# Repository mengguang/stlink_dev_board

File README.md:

# stlink_dev_board
I know nothing about this project.

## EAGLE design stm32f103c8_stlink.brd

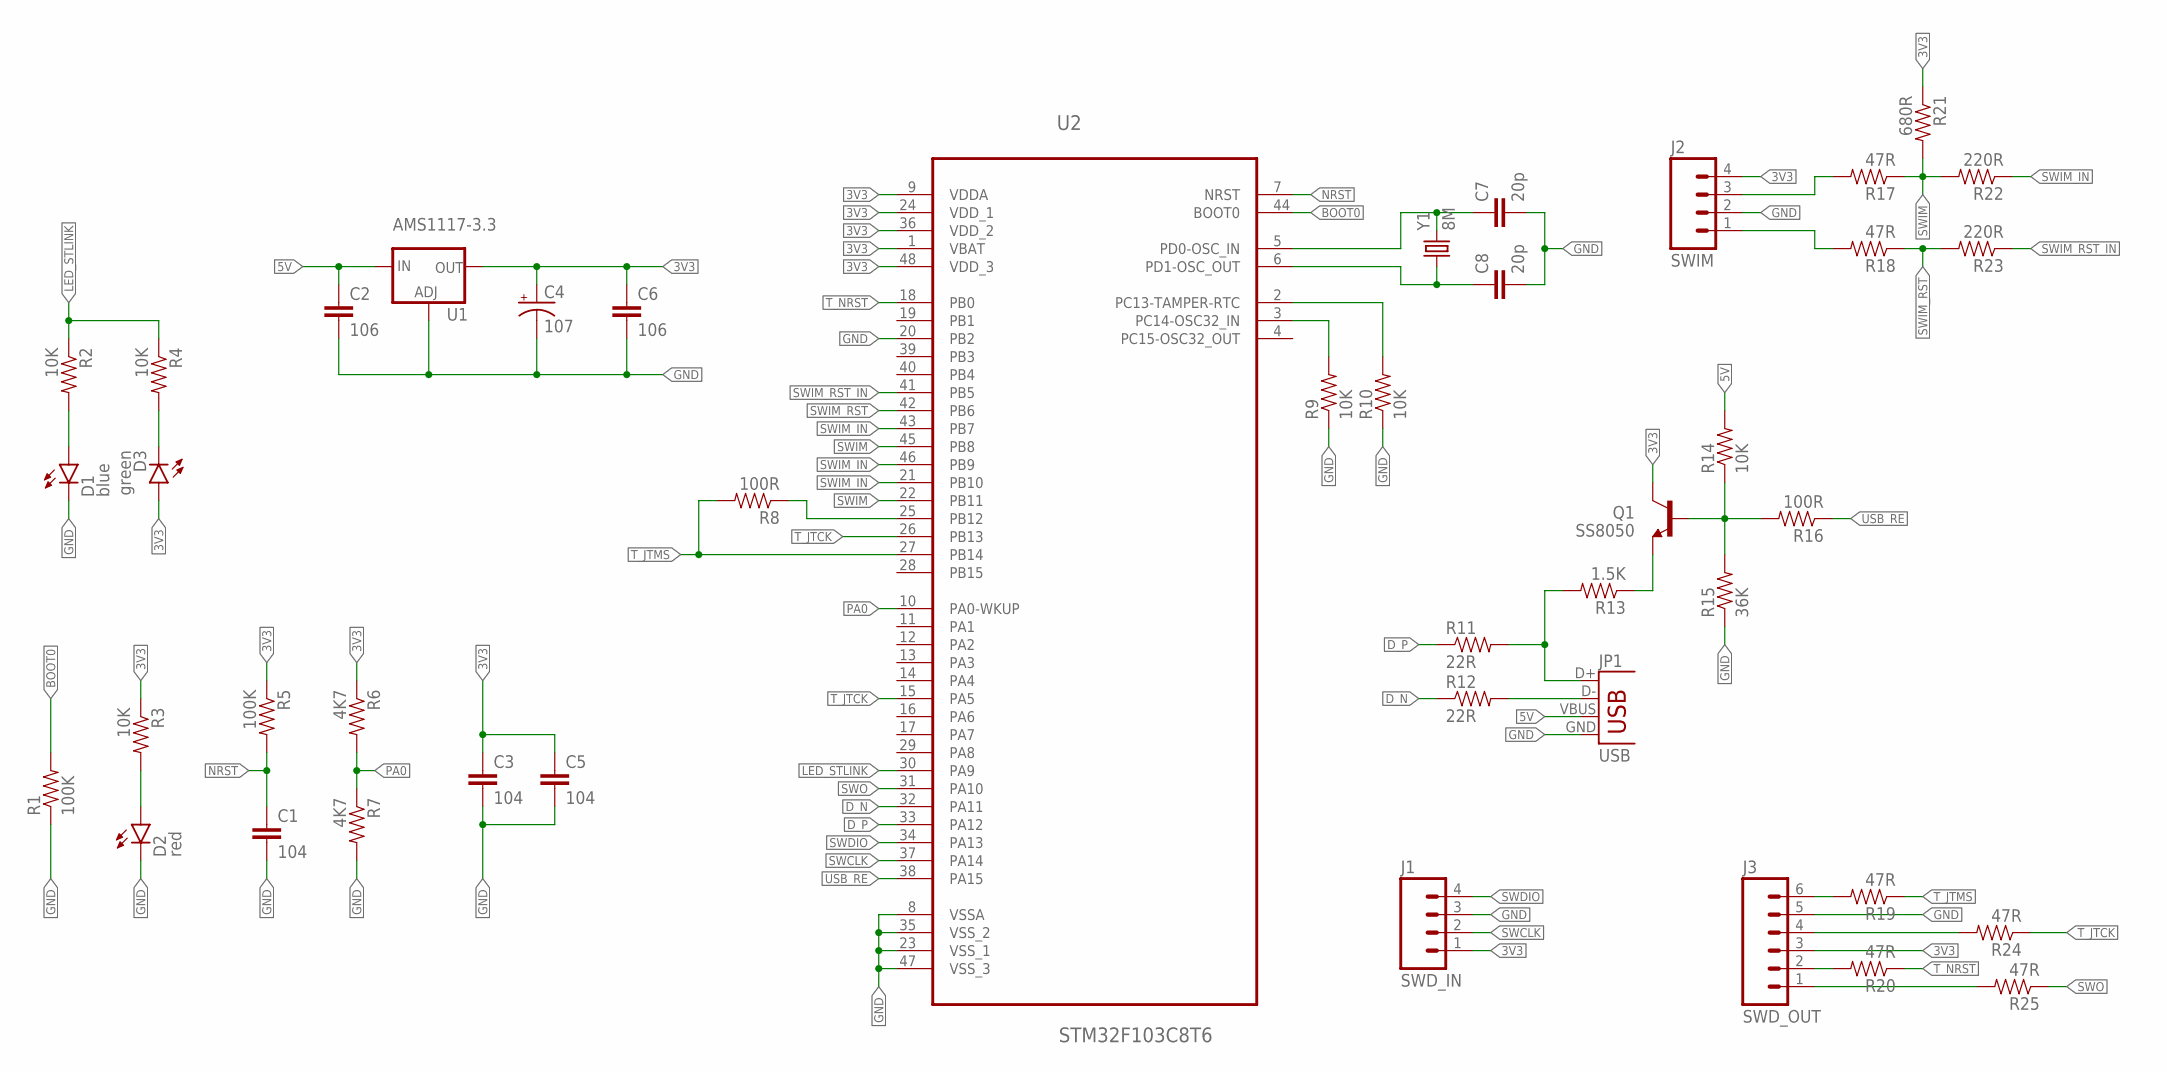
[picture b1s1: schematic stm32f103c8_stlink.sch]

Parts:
C1, C3, C5: 104; 0603-CAP
C2, C6: 106; 0603-CAP
C4: 107; EIA3528
C7, C8: 20p; 0603-CAP
D1: blue; LED-0603-SEEED
D2: red; LED-0603-SEEED
D3: green; LED-0603-SEEED
J1: SWD_IN; 1X04_NO_SILK
J2: SWIM; 1X04_NO_SILK
J3: SWD_OUT; 1X06_NO_SILK
JP1: USB; MICROUSB-U-F-M5DD-Y-1
Q1: SS8050; SOT23-3
R1, R5: 100K; 0603-RES
R2, R3, R4, R9, R10, R14: 10K; 0603-RES
R6, R7: 4K7; 0603-RES
R8, R16: 100R; 0603-RES
R11, R12: 22R; 0603-RES
R13: 1.5K; 0603-RES
R15: 36K; 0603-RES
R17, R18, R19, R20, R24, R25: 47R; 0603-RES
R21: 680R; 0603-RES
R22, R23: 220R; 0603-RES
U1: AMS1117-3.3; SOT223
U2: STM32F103C8T6; LQFP-48
Y1: 8M; HC49US

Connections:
3V3: C3.1, C4.A (+), C5.1, C6.1, D3.+ (A), J1.1, J2.4, J3.3, Q1.3 (C), R3.1, R5.1, R6.1, R21.1, U1.2 (OUT), U1.4 (OUT), U2.1 (VBAT), U2.9 (VDDA), U2.24 (VDD_1), U2.36 (VDD_2), U2.48 (VDD_3)
5V: C2.1, JP1.VBUS, R14.2, U1.3 (IN)
BOOT0: R1.2, U2.44 (BOOT0)
D_N: R12.1, U2.32 (PA11)
D_P: R11.1, U2.33 (PA12)
GND: C1.2, C2.2, C3.2, C4.C (-), C5.2, C6.2, C7.2, C8.2, D1.- (C), D2.- (C), J1.3, J2.2, J3.5, JP1.GND, R1.1, R7.2, R9.1, R10.1, R15.1, U1.1 (ADJ), U2.8 (VSSA), U2.20 (PB2), U2.23 (VSS_1), U2.35 (VSS_2), U2.47 (VSS_3)
LED_STLINK: R2.1, R4.1, U2.30 (PA9)
unnamed: J3.6, R19.2
unnamed: J2.3, R17.2
unnamed: C7.1, U2.5 (PD0-OSC_IN), Y1.2
unnamed: C8.1, U2.6 (PD1-OSC_OUT), Y1.1
unnamed: D2.+ (A), R3.2
unnamed: Q1.2 (E), R13.1
unnamed: D1.+ (A), R2.2
unnamed: R10.2, U2.2 (PC13-TAMPER-RTC)
unnamed: R9.2, U2.3 (PC14-OSC32_IN)
unnamed: D3.- (C), R4.2
unnamed: Q1.1 (B), R14.1, R15.2, R16.2
unnamed: R8.1, U2.25 (PB12)
unnamed: J2.1, R18.2
unnamed: J3.4, R24.2
unnamed: J3.2, R20.2
unnamed: J3.1, R25.2
NRST: C1.1, R5.2, U2.7 (NRST)
PA0: R6.2, R7.1, U2.10 (PA0-WKUP)
SWCLK: J1.2, U2.37 (PA14)
SWDIO: J1.4, U2.34 (PA13)
SWIM: R17.1, R21.2, R22.2, U2.22 (PB11), U2.45 (PB8)
SWIM_IN: R22.1, U2.21 (PB10), U2.43 (PB7), U2.46 (PB9)
SWIM_RST: R18.1, R23.2, U2.42 (PB6)
SWIM_RST_IN: R23.1, U2.41 (PB5)
SWO: R25.1, U2.31 (PA10)
T_JTCK: R24.1, U2.15 (PA5), U2.26 (PB13)
T_JTMS: R8.2, R19.1, U2.27 (PB14)
T_NRST: R20.1, U2.18 (PB0)
USB_N: JP1.D-, R12.2
USB_P: JP1.D+, R11.2, R13.2
USB_RE: R16.1, U2.38 (PA15)

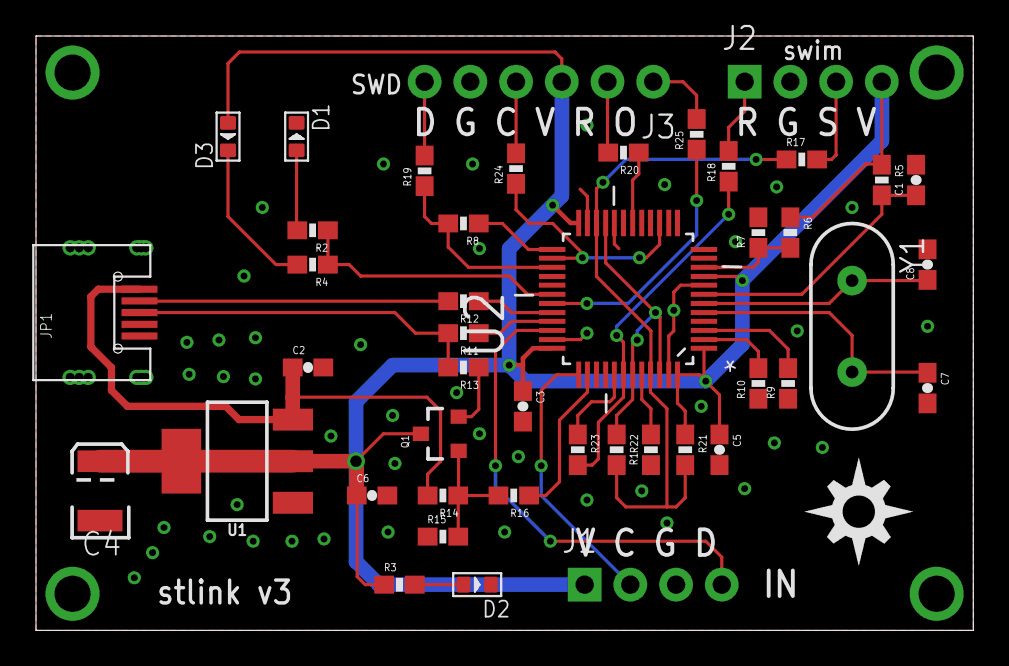
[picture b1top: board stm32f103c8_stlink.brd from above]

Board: 2 copper layers, 52.1 x 33.0 mm, 45 parts (0 on the bottom side), 38 nets.

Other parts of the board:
U$1: DIYNOVA_LOGO

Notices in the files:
parts and their libraries:
SparkFun-Connectors: Licensing: Creative Commons ShareAlike 4.0 International - https://creativecommons.org/licenses/by-sa/4.0
